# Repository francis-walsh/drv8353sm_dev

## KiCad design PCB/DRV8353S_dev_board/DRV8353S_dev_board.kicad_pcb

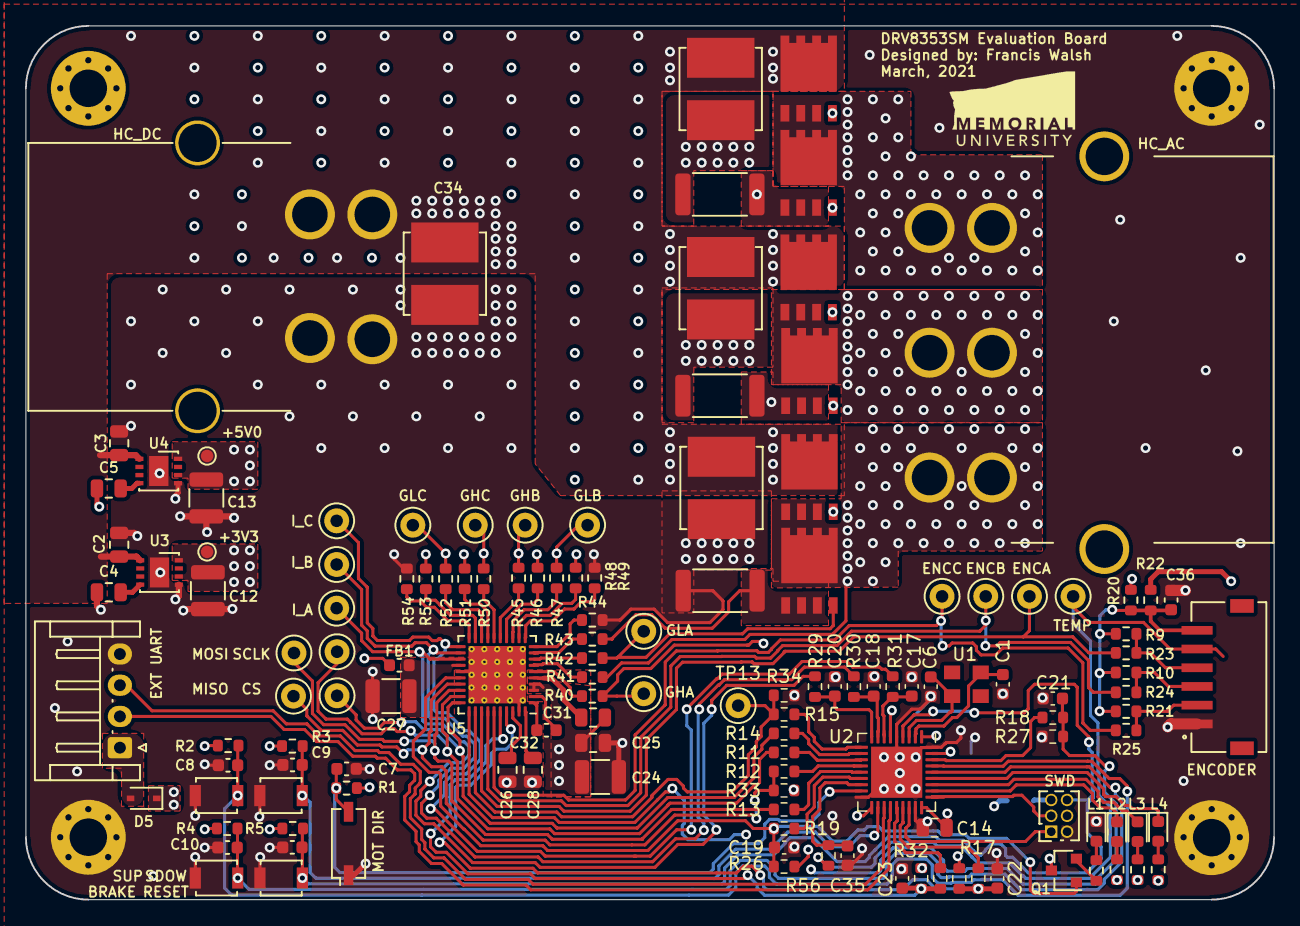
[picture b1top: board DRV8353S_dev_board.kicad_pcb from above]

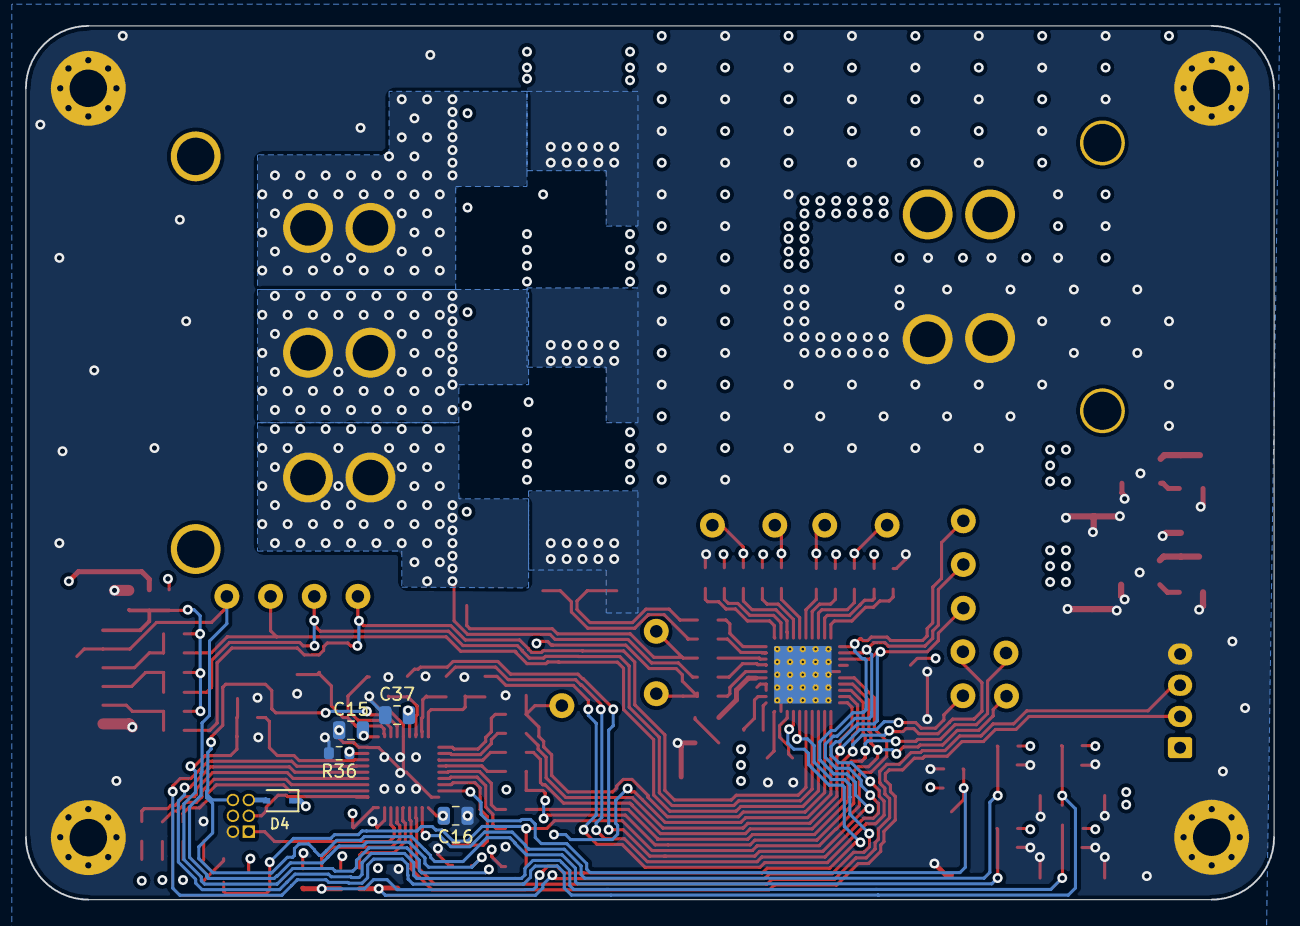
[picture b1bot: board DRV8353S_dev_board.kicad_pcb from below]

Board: 4 copper layers, 100.0 x 70.0 mm, 141 parts (5 on the bottom side), 96 nets.

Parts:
+3V3, +5V0: SMD; TestPoint_Pad_D1.0mm
BRAKE: B3U; SW_SPST_B3U-1000P
C1, C6: 12pF; C_0603_1608Metric
C2, C3, C14, C15, C16, C26, C28, C31, C37: 1uF; C_0805_2012Metric
C4, C5, C25: 0.1uF; C_0805_2012Metric
C7, C8, C9, C10, C11, C17, C18, C19, C20, C21, C22, C23, C35, C36: 22nF; C_0603_1608Metric
C12, C13, C24, C27: 10uF; C_1210_3225Metric
C29, C30, C33, C34: 10uF; bridge_caps
C32: 47nF; C_0603_1608Metric
CS: THT; keystone_5001
D4, D5: BAT46; D_SOD-323
ENCA: THT; keystone_5001
ENCB: THT; keystone_5001
ENCC: THT; keystone_5001
ENCODER: MOT_LC; JST_S6B-ZR-SM4A-TF(LF)(SN)
EXT UART: EXT_CMD; JST_EH_S4B-EH_1x04_P2.50mm_Horizontal
FB1: FB; L_0603_1608Metric
GHA: THT; keystone_5001
GHB: THT; keystone_5001
GHC: THT; keystone_5001
GLA: THT; keystone_5001
GLB: THT; keystone_5001
GLC: THT; keystone_5001
HC_AC: PHASE; MOLEX_0428203213
HC_DC: HC_POWER; MOLEX_428202213
I_A: THT; keystone_5001
I_B: THT; keystone_5001
I_C: THT; keystone_5001
L1, L2: RD; LED_0603_1608Metric
L3, L4: GN; LED_0603_1608Metric
MISO: THT; keystone_5001
MOSI: THT; keystone_5001
MOT DIR: DIP; SW_DIP_SPSTx01_Slide_Copal_CHS-01A_W5.08mm_P1.27mm_JPin
Q1: BSS84; SOT-23
Q2, Q3, Q4, Q5, Q6, Q7: CSD19502
R1, R2, R3, R4, R5, R9, R10, R21, R26, R27, R28, R32, R33, R34, R35, R36: 2.2k; R_0603_1608Metric
R6, R7, R8: 1k; R_0603_1608Metric
R11, R12, R13, R14, R15, R16, R17, R18, R19, R20, R22, R23, R24, R25, R40, R41, R42, R43, R44, R45, R46, R47, R48, R49, R50, R51, R52, R53, R54: 0; R_0603_1608Metric
R29, R30, R31, R56: 330; R_0603_1608Metric
R38, R39, R55: 500u; R_2512_6332Metric
RESET: B3U; SW_SPST_B3U-1000P
SCLK: THT; keystone_5001
SDOW: B3U; SW_SPST_B3U-1000P
SUP: B3U; SW_SPST_B3U-1000P
SWD: SWD; PinSocket_2x03_P1.27mm_Vertical
TEMP: THT; keystone_5001
TP13: THT; keystone_5001
U1: ECS-33B
U2: STM32F103TBUx; QFN-36-1EP_6x6mm_P0.5mm_EP4.1x4.1mm
U3: MIC5283-3.3ML-TR; DFN-8-1EP_3x3mm_P0.65mm_EP1.55x2.4mm
U4: MIC5283-5.0ML-TR; DFN-8-1EP_3x3mm_P0.65mm_EP1.55x2.4mm
U5: DRV8353SM; QFN-40-1EP_6x6mm_P0.5mm_EP4.6x4.6mm_ThermalVias

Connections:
+3V3: +3V3.1, C12.1, C14.2, C15.2, C16.2, C37.2, D4.1, D5.1, FB1.2, Q1.3, R1.2, R2.2, R3.2, R4.2, R5.2, R6.2, R7.2, R8.2, R20.1, R26.2, R28.2, R32.2, R33.2, U2.1, U2.6, U2.19, U2.27, U3.6, U3.8
+5V: +5V0.1, C13.1, R22.1, U4.6, U4.8
/DIRECTION: C23.2, R16.2, R32.1, U5.36
/DIRECTION_DIP: C7.2, MOT DIR.2, R1.1, U2.17
/DIRECTION_JMP: R16.1, U2.23
/DRV8353_EN: C21.2, R18.2, R27.2, U5.31
/DRV8353_EN_JMP: R18.1, U2.34
/EXT_UART_RX: EXT UART.2, U2.22
/EXT_UART_TX: EXT UART.3, U2.21
/GATE_HI_A: GHA.1, Q2.2, R40.2
/GATE_HI_B: GHB.1, Q4.2, R45.2
/GATE_HI_C: GHC.1, Q6.2, R50.2
/GATE_LO_A: GLA.1, Q3.2, R42.2
/GATE_LO_B: GLB.1, Q5.2, R47.2
/GATE_LO_C: GLC.1, Q7.2, R52.2
/HALLA: ENCA.1, R23.2, U5.33
/HALLA_JMP: ENCODER.4, R9.1, R23.1
/HALLB: ENCB.1, R24.2, U5.34
/HALLB_JMP: ENCODER.3, R10.1, R24.1
/HALLC: ENCC.1, R25.2, U5.35
/HALLC_JMP: ENCODER.2, R21.1, R25.1
/I_PHASE_A: I_A.1, R29.2, U5.23
/I_PHASE_A_JMP: C20.1, R29.1, U2.9
/I_PHASE_B: I_B.1, R30.2, U5.22
/I_PHASE_B_JMP: C18.1, R30.1, U2.8
/I_PHASE_C: I_C.1, R31.2, U5.21
/I_PHASE_C_JMP: C17.1, R31.1, U2.7
/MISO: MISO.1, R12.2, R33.1, U5.27
/MISO_JMP: R12.1, U2.13
/MOSI: MOSI.1, R13.2, U5.28
/MOSI_JMP: R13.1, U2.14
/MOT_A: HC_AC.3, Q2.3, Q3.1, R41.2
/MOT_B: HC_AC.2, Q4.3, Q5.1, R46.2
/MOT_C: HC_AC.1, Q6.3, Q7.1, R51.2
/MOT_TEMP: ENCODER.5, R56.2, TEMP.1
/MOT_TEMP_JMP: C35.1, R56.1, U2.16
/SCLK: R11.2, SCLK.1, U5.29
/SCLK_JMP: R11.1, U2.12
/SHUNT_POS_A: Q3.3, R38.1, R43.2
/SHUNT_POS_B: Q5.3, R39.1, R48.2
/SHUNT_POS_C: Q7.3, R53.2, R55.1
/SPEED_PWM: R15.2, R34.2, TP13.1, U5.32
/SPEED_PWM_JMP: R15.1, U2.10
/SWCLK: SWD.3, U2.28
/SWDIO: SWD.1, U2.25
/XTAL_IN: C1.1, U1.1, U2.2
/XTAL_OUT: C6.1, U1.3, U2.3
/~BRAKE: C22.2, R17.2, R28.1, U5.37
/~BRAKE_JMP: R17.1, U2.24
/~BRAKE_PB: BRAKE.2, C10.2, R4.1, U2.32
/~DRV8353_CS: CS.1, R14.2, U5.30
/~DRV8353_CS_JMP: R14.1, U2.11
/~DRV8353_FAULT: C19.2, Q1.1, R19.2, R26.1, U5.26
/~DRV8353_FAULT_JMP: R19.1, U2.15
/~LED_DIR: L4.1, U2.31
/~LED_SPEED: L3.1, U2.30
/~RESET_PB: C11.2, R5.1, RESET.2, SWD.6, U2.4
/~SPEED_DOWN_PB: C9.2, R3.1, SDOW.2, U2.20
/~SPEED_UP_PB: C8.2, R2.1, SUP.2, U2.33
/~SYS_FAULT: L2.1, U2.29
GND: BRAKE.1, C1.2, C2.1, C3.1, C4.1, C5.1, C6.2, C7.1, C8.1, C9.1, C10.1, C11.1, C12.2, C13.2, C14.1, C15.1, C16.1, C17.2, C18.2, C19.1, C20.2, C21.1, C22.1, C23.1, C24.1, C25.2, C26.2, C27.2, C28.2, C29.2, C30.2, C33.2, C34.2, C35.2, C36.2, C37.1, ENCODER.1, EXT UART.4, HC_DC.1, L1.1, MOT DIR.1, R27.1, R34.1, R36.2, R38.2, R39.2, R44.2, R49.2, R54.2, R55.2, RESET.1, SDOW.1, SUP.1, SWD.2, U2.5, U2.18, U2.26, U2.36, U2.37, U3.5, U3.9, U4.5, U4.9, U5.25, U5.39, U5.41
unnamed: C4.2, U3.4
unnamed: C5.2, U4.4
unnamed: C26.1, U5.38
unnamed: C27.1, FB1.1, U5.24
unnamed: C28.1, U5.40
unnamed: C31.2, U5.5
unnamed: C32.1, U5.2
unnamed: C32.2, U5.1
unnamed: C36.1, ENCODER.6, R9.2, R10.2, R20.2, R21.2, R22.2
unnamed: L4.2, R6.1
unnamed: L3.2, R7.1
unnamed: L2.2, R8.1
unnamed: D4.2, SWD.5
unnamed: D5.2, EXT UART.1
unnamed: L1.2, R35.1
unnamed: Q1.2, R35.2
unnamed: R36.1, U2.35
unnamed: R40.1, U5.6
unnamed: R41.1, U5.7
unnamed: R42.1, U5.8
unnamed: R43.1, U5.9
unnamed: R44.1, U5.10
unnamed: R45.1, U5.15
unnamed: R46.1, U5.14
unnamed: R47.1, U5.13
unnamed: R48.1, U5.12
unnamed: R49.1, U5.11
unnamed: R50.1, U5.16
unnamed: R51.1, U5.17
unnamed: R52.1, U5.18
unnamed: R53.1, U5.19
unnamed: R54.1, U5.20
unnamed: U3.2, U3.3, U3.7
unnamed: U4.2, U4.3, U4.7
Vdrive: C2.2, C3.2, C24.2, C25.1, C29.1, C30.1, C31.1, C33.1, C34.1, HC_DC.2, Q2.1, Q4.1, Q6.1, U3.1, U4.1, U5.3, U5.4

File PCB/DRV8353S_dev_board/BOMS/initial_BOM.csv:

Reference, Quantity, Value, Digikey
C1 C6 ,2,12pF,478-10188-1-ND
C2 C3 C14 C15 C16 C26 C28 C31 ,8,1uF,478-12143-1-ND
C7 C8 C9 C10 C11 C17 C18 C19 C20 C21 C22 C23 C35 C36 ,14,22nF,445-5663-1-ND
C4 C5 C25 ,3,0.1uF,1276-6840-1-ND
C12 C13 C24 C27 ,4,10uF,445-181609-1-ND
C29 C30 C33 C34 ,4,10uF,1189-3804-1-ND
C32 ,1,47nF,311-4050-1-ND
D1 D2 ,2,GN,732-4971-1-ND
D3 D6 ,2,RD,732-4978-1-ND
D4 D5 ,2,BAT46,497-6653-1-ND
FB1 ,1,FB,732-1593-1-ND
J1 ,1,HC_POWER,WM6461-ND
J2 ,1,MOT_LC,455-1673-ND
J3 ,1,SWD,S9015E-03-ND
J4 ,1,EXT_CMD,455-1627-ND
J5 ,1,PHASE,WM11180-ND
Q1 ,1,BSS84,BSS84-FDICT-ND
Q2 Q3 Q4 Q5 Q6 Q7 ,6,CSD19502,296-37194-1-ND
R1 R2 R3 R4 R5 R9 R10 R21 R26 R27 R28 R32 R33 R34 R35 ,15,2.2k,
R38 R39 R55 ,3,500u,YAG5784CT-ND
R11 R12 R13 R14 R15 R16 R17 R18 R19 R20 R22 R23 R24 R25 R40 R41 R42 R43 R44 R45 R46 R47 R48 R49 R50 R51 R52 R53 R54 ,29,0,RMCF0603ZT0R00CT-ND
R29 R30 R31 R56 ,4,330,CR0603-JW-331ELFCT-ND
R6 R7 R8 ,3,1k,
SW1 SW2 SW3 SW4 ,4,B3U,SW1020CT-ND
SW5 ,1,DIP,563-1003-1-ND
TP3 TP4 TP5 TP6 TP7 TP8 TP9 TP10 TP11 TP12 TP13 TP14 TP15 TP16 TP17 TP18 TP19 TP20 ,18,THT,36-5001-ND
U1 ,1,ECS-33B,50-ECS-320-12-33B-7KM-CT-ND
U2 ,1,STM32F103TBUx,497-11534-ND
U3 ,1,MIC5283-3.3ML-TR,MIC5283-3.3YML-CT-ND
U4 ,1,MIC5283-5.0ML-TR,576-4343-1-ND
U5 ,1,DRV8353SM,296-DRV8353SMRTATCT-ND
,,,
Other Cap 1,3,,478-9622-1-ND
Other cap 2,3,,478-12101C475K4Z2ACT-ND
SWD cable assembly,1,,SAM8668-ND
Phase Conn terminals,3,,WM9166CT-ND
Phase conn housing,1,,WM1928-ND
DC Connector Assembly,1,,900-0369240203-ND

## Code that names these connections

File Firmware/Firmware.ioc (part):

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Mcu.Name=STM32F103T(8-B)Ux
Mcu.Package=VFQFPN36
Mcu.UserName=STM32F103TBUx
PA0-WKUP.GPIOParameters=GPIO_Label
PA0-WKUP.GPIO_Label=PHASE_C
PA0-WKUP.Signal=ADCx_IN0
PA1.GPIOParameters=GPIO_Label
PA1.GPIO_Label=PHASE_B
PA1.Signal=ADCx_IN1
PA10.Mode=Asynchronous
PA10.Signal=USART1_RX
PA11.GPIOParameters=GPIO_Label
PA11.GPIO_Label=DRV_DIR
PA11.Signal=GPIO_Output
PA12.GPIOParameters=GPIO_Label
PA12.GPIO_Label=DRV_BRAKE
PA12.Signal=GPIO_Output
PA13.Mode=Serial_Wire
PA13.Signal=SYS_JTMS-SWDIO
PA14.Mode=Serial_Wire
PA14.Signal=SYS_JTCK-SWCLK
PA15.GPIOParameters=GPIO_Label
PA15.GPIO_Label=LED_FAULT
PA15.Signal=GPIO_Output
PA2.GPIOParameters=GPIO_Label
PA2.GPIO_Label=PHASE_A
PA2.Signal=ADCx_IN2
PA3.GPIOParameters=GPIO_Label
PA3.GPIO_Label=SPEED_PWM
PA3.Signal=S_TIM2_CH4
PA4.GPIOParameters=GPIO_Label
PA4.GPIO_Label=DRV_CS
PA4.Signal=GPIO_Output
PA5.Mode=Full_Duplex_Master
PA5.Signal=SPI1_SCK
PA6.Mode=Full_Duplex_Master
PA6.Signal=SPI1_MISO
PA7.Mode=Full_Duplex_Master
PA7.Signal=SPI1_MOSI
PA8.GPIOParameters=GPIO_Label
PA8.GPIO_Label=S_DOWN_PB
PA8.Signal=GPIO_Input
PA9.Mode=Asynchronous
PA9.Signal=USART1_TX
PB0.GPIOParameters=GPIO_Label
PB0.GPIO_Label=DRV_FAULT
PB0.Signal=GPXTI0
PB1.GPIOParameters=GPIO_Label
PB1.GPIO_Label=MOT_TEMP
PB1.Signal=ADCx_IN9
PB2.GPIOParameters=GPIO_Label
PB2.GPIO_Label=DIR_DIP
PB2.Signal=GPIO_Input
PB3.GPIOParameters=GPIO_Label
PB3.GPIO_Label=LED_SPEED
PB3.Signal=S_TIM2_CH2
PB4.GPIOParameters=GPIO_Label
PB4.GPIO_Label=LED_DIR
PB4.Signal=GPIO_Output
PB5.GPIOParameters=GPIO_Label
PB5.GPIO_Label=BRAKE_PB
PB5.Signal=GPIO_Input
PB6.GPIOParameters=GPIO_Label
PB6.GPIO_Label=S_UP_PB
PB6.Signal=GPIO_Input
PB7.GPIOParameters=GPIO_Label
PB7.GPIO_Label=DRV_EN
PB7.Signal=GPIO_Output
PD0-OSC_IN.Mode=HSE-External-Oscillator
PD0-OSC_IN.Signal=RCC_OSC_IN
PD1-OSC_OUT.Mode=HSE-External-Oscillator
PD1-OSC_OUT.Signal=RCC_OSC_OUT
board=custom

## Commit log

2021-02-26 Initial commit
    Work done so far.
2021-02-27 High Current Routing planning
    Planning how the high current routing will work with the gate drive signals
2021-03-01 more routing work
2021-03-01 Final (?) layout
2021-03-02 Final Routing
    Moved around encoder stuff. Also added decoupling capacitor near encoder connector.
2021-03-02 High Current Routing
2021-03-02 Most DRV routing done.
2021-03-03 Finished routing (?)
    All signals routed. No DRC errors.
2021-03-03 final final routing
2021-03-03 Fixed silkscreen and added BOM
2021-03-05 Changed MCU due to low digikey stock. Also new routing
2021-03-08 updated MCU due to low digi stock. This was bad routing to get new MCU pinout
2021-03-08 Good routing
2021-03-09 As ordered PCB
